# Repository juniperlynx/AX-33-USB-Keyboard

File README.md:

# AX-33 Keyboard controller
This is a USB keyboard controller for the membrane key mechanism found in the Brother AX-33 Typewriter.

The design is based on the one described in Ruiqi Mao's [keyboard-pcb-guide](https://github.com/ruiqimao/keyboard-pcb-guide) and uses Hasu's [component library](https://github.com/tmk/kicad_lib_tmk) and [footprint library](https://github.com/tmk/keyboard_parts.pretty).

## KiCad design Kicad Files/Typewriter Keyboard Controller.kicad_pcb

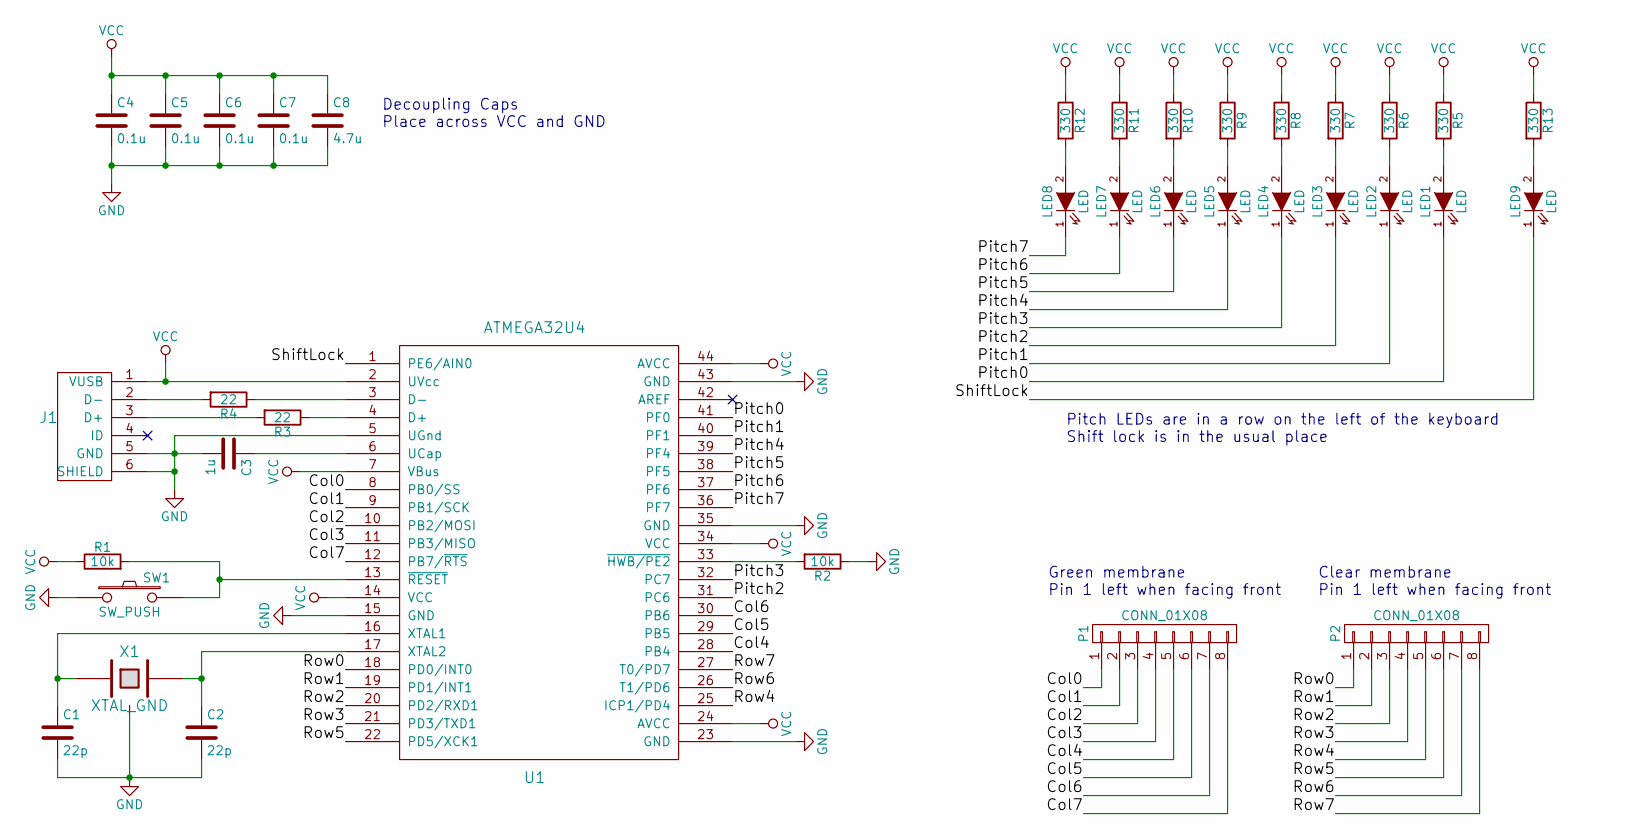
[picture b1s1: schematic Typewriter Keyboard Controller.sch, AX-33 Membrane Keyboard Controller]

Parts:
C1, C2: 22p; C_0402
C3: 1u; C_0402
C4, C5, C6, C7: 0.1u; C_0402
C8: 4.7u; C_0402
J1: USB_mini_micro_B; USB_miniB_hirose_5S8
LED1, LED2, LED3, LED4, LED5, LED6, LED7, LED8, LED9: LED; LED-3MM
P1, P2: CONN_01X08; Pin_Header_Straight_1x08
R1, R2: 10k; R_0402
R3, R4: 22; R_0402
R5, R6, R7, R8, R9, R10, R11, R12, R13: 330; R_0402
SW1: SW_PUSH; SW_SPST_PTS645
U1: ATMEGA32U4; TQFP-44_10x10mm_Pitch0.8mm
X1: XTAL_GND; crystal_FA238-TSX3225

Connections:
/Col0: P1.1, U1.8 (PB0/SS)
/Col1: P1.2, U1.9 (PB1/SCK)
/Col2: P1.3, U1.10 (PB2/MOSI)
/Col3: P1.4, U1.11 (PB3/MISO)
/Col4: P1.5, U1.28 (PB4)
/Col5: P1.6, U1.29 (PB5)
/Col6: P1.7, U1.30 (PB6)
/Col7: P1.8, U1.12 (PB7/~RTS)
/Pitch0: LED1.1 (K), U1.41 (PF0)
/Pitch1: LED2.1 (K), U1.40 (PF1)
/Pitch2: LED3.1 (K), U1.31 (PC6)
/Pitch3: LED4.1 (K), U1.32 (PC7)
/Pitch4: LED5.1 (K), U1.39 (PF4)
/Pitch5: LED6.1 (K), U1.38 (PF5)
/Pitch6: LED7.1 (K), U1.37 (PF6)
/Pitch7: LED8.1 (K), U1.36 (PF7)
/Row0: P2.1, U1.18 (PD0/INT0)
/Row1: P2.2, U1.19 (PD1/INT1)
/Row2: P2.3, U1.20 (PD2/RXD1)
/Row3: P2.4, U1.21 (PD3/TXD1)
/Row4: P2.5, U1.25 (ICP1/PD4)
/Row5: P2.6, U1.22 (PD5/XCK1)
/Row6: P2.7, U1.26 (T1/PD6)
/Row7: P2.8, U1.27 (T0/PD7)
/ShiftLock: LED9.1 (K), U1.1 (PE6/AIN0)
GND: C1.2, C2.2, C3.2, C4.2, C5.2, C6.2, C7.2, C8.2, J1.5 (GND), J1.6 (SHIELD), R2.1, SW1.1, U1.5 (UGnd), U1.15 (GND), U1.23 (GND), U1.35 (GND), U1.43 (GND), X1.3
unnamed: C1.1, U1.16 (XTAL1), X1.1
unnamed: C2.1, U1.17 (XTAL2), X1.2
unnamed: C3.1, U1.6 (UCap)
unnamed: J1.2 (D-), R4.2
unnamed: J1.3 (D+), R3.2
unnamed: LED1.2 (A), R5.2
unnamed: LED2.2 (A), R6.2
unnamed: LED3.2 (A), R7.2
unnamed: LED4.2 (A), R8.2
unnamed: LED5.2 (A), R9.2
unnamed: LED6.2 (A), R10.2
unnamed: LED7.2 (A), R11.2
unnamed: LED8.2 (A), R12.2
unnamed: LED9.2 (A), R13.2
unnamed: R1.2, SW1.2, U1.13 (~RESET)
unnamed: R2.2, U1.33 (~HWB/PE2)
unnamed: R3.1, U1.4 (D+)
unnamed: R4.1, U1.3 (D-)
VCC: C4.1, C5.1, C6.1, C7.1, C8.1, J1.1 (VUSB), R1.1, R5.1, R6.1, R7.1, R8.1, R9.1, R10.1, R11.1, R12.1, R13.1, U1.2 (UVcc), U1.7 (VBus), U1.14 (VCC), U1.24 (AVCC), U1.34 (VCC), U1.44 (AVCC)

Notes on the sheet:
Green membrane Pin 1 left when facing front
Clear membrane Pin 1 left when facing front
Decoupling Caps Place across VCC and GND
Pitch LEDs are in a row on the left of the keyboard Shift lock is in the usual place

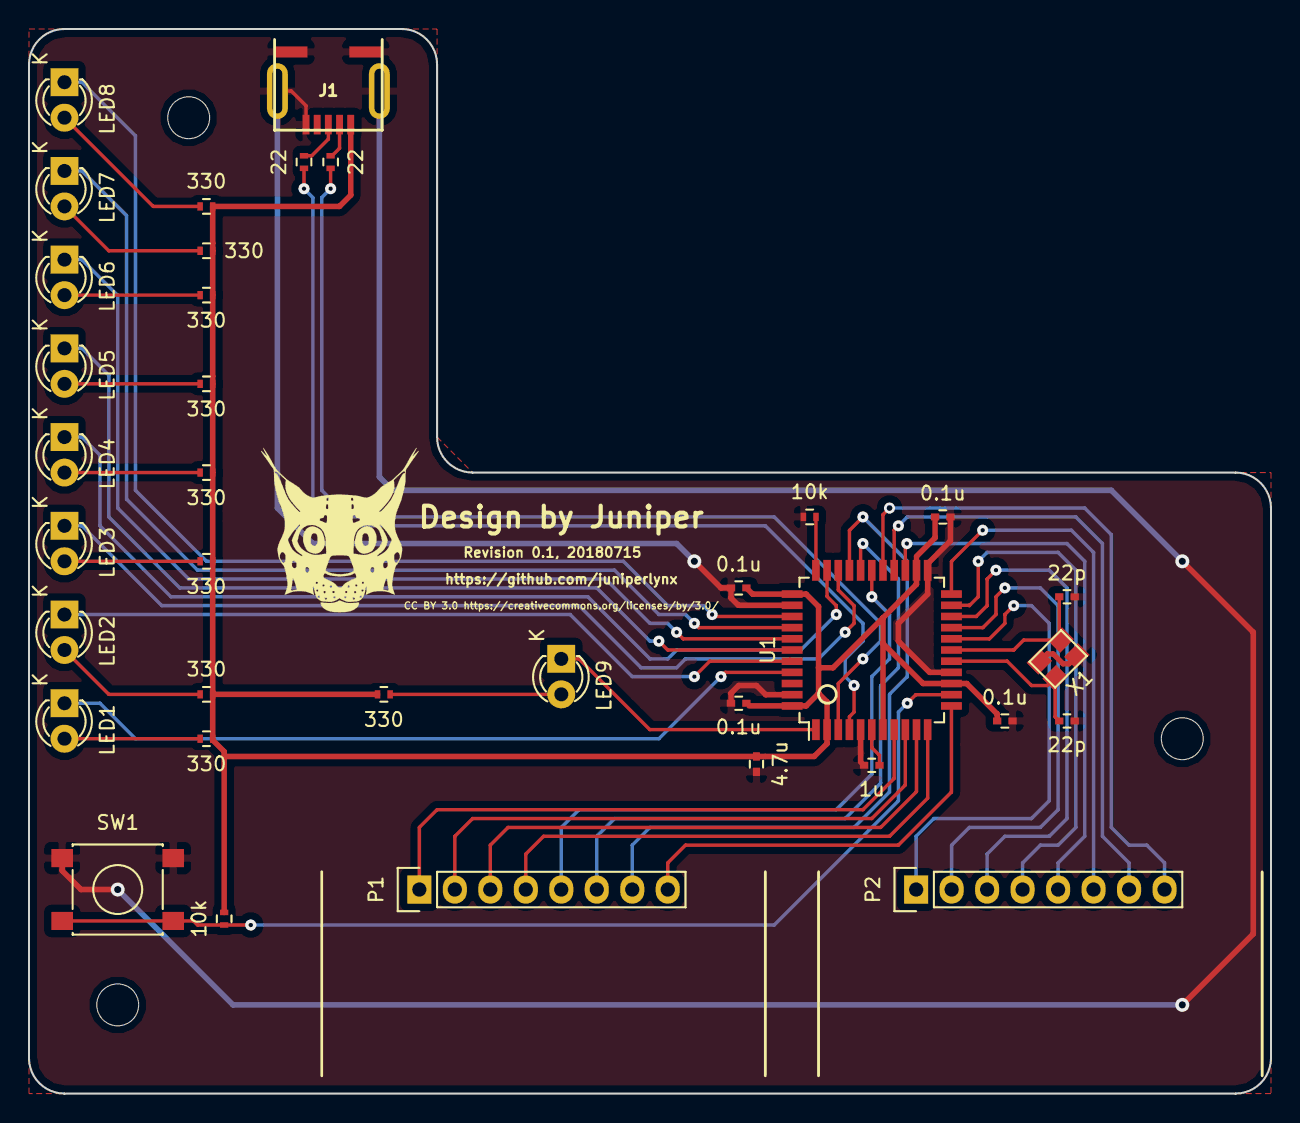
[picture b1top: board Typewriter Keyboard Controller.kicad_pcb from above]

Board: 2 copper layers, 88.9 x 76.2 mm, 36 parts (0 on the bottom side), 45 nets.

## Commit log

2018-07-18 Export BOM
2018-07-18 Make mouting holes smaller
2018-07-18 Export Gerbers
2018-08-11 Add descriptive files from keyboard-layout-editor
2018-08-29 update to KiCad 5
2018-09-28 Switch to current QMK

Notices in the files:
Kicad Files/Typewriter Keyboard Controller.kicad_pcb:
CC BY 3.0 https://creativecommons.org/licenses/by/3.0
